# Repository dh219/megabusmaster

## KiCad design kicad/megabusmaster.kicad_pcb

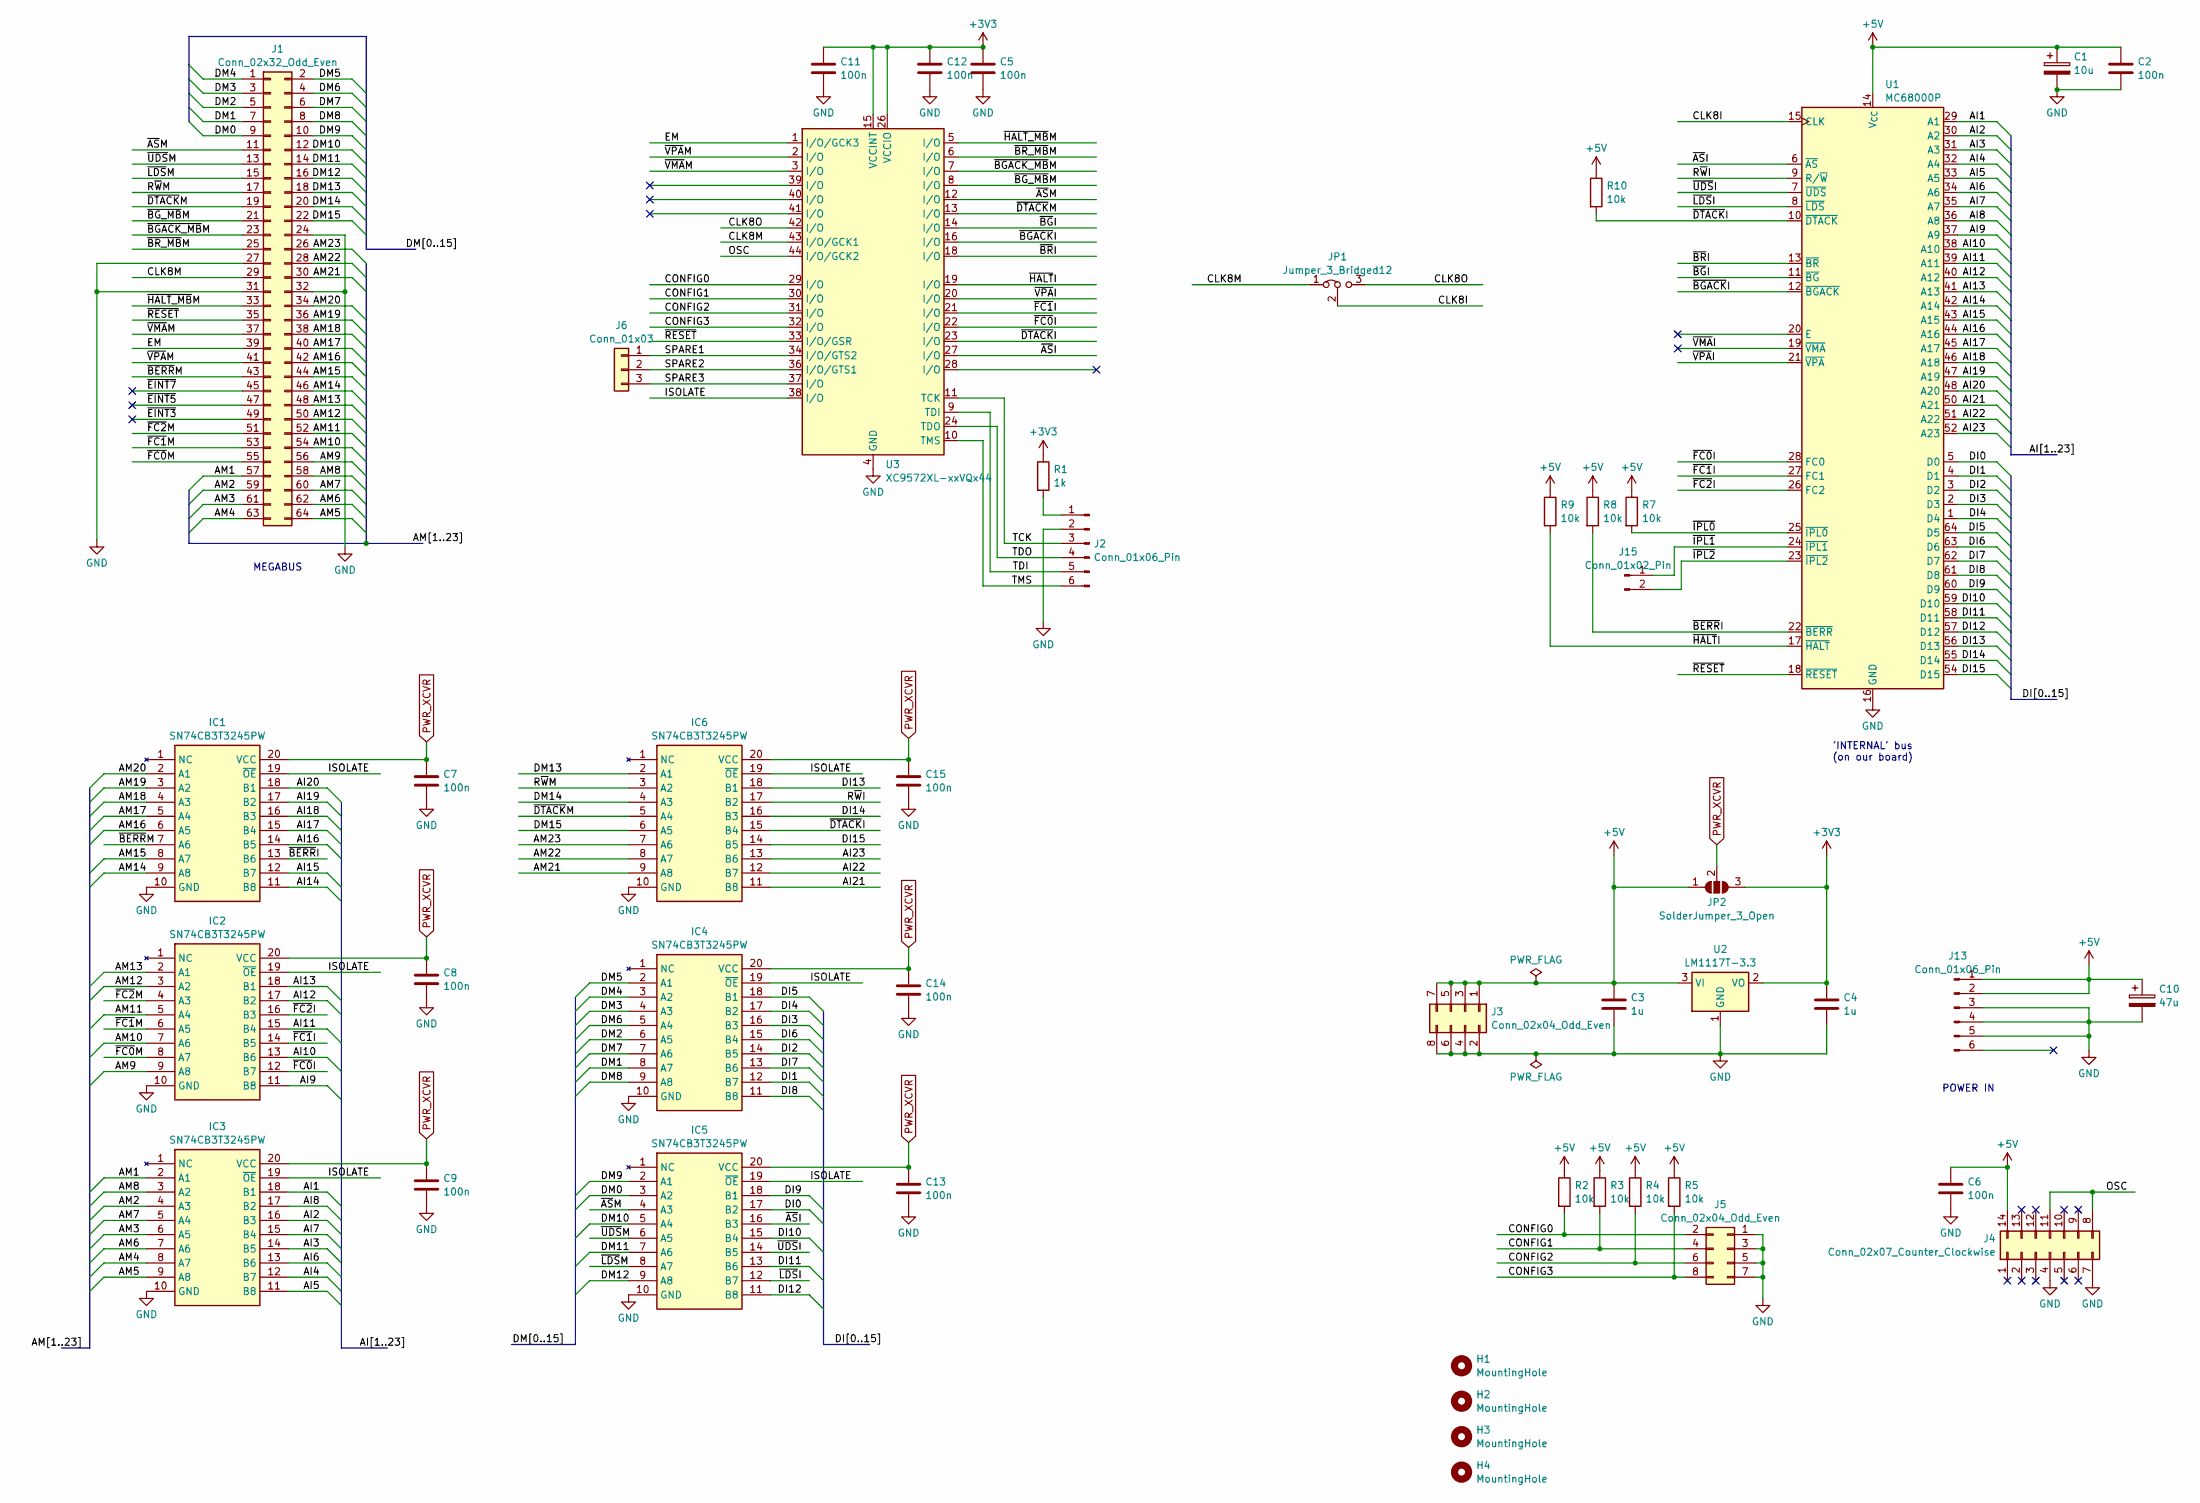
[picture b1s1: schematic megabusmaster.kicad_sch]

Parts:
C1: 10u; CP_Radial_D5.0mm_P2.50mm
C2, C5, C6, C7, C8, C9, C11, C12, C13, C14, C15: 100n; C_0805_2012Metric_Pad1.18x1.45mm_HandSolder
C3, C4: 1u; C_0805_2012Metric_Pad1.18x1.45mm_HandSolder
C10: 47u; CP_Radial_D5.0mm_P2.50mm
H1, H2, H3, H4: MountingHole; MountingHole_3.2mm_M3
IC1, IC2, IC3, IC4, IC5, IC6: SN74CB3T3245PW; TSSOP-20_4.4x6.5mm_P0.65mm; Manufacturer_Part_Number SN74CB3T3245PW; Mouser Part Number 595-SN74CB3T3245PW
J1: Conn_02x32_Odd_Even; PinSocket_2x32_P2.54mm_Vertical
J2, J13: Conn_01x06_Pin; PinHeader_1x06_P2.54mm_Vertical
J3, J5: Conn_02x04_Odd_Even; PinHeader_2x04_P2.54mm_Vertical
J4: Conn_02x07_Counter_Clockwise; DIP-14_W7.62mm_Socket
J6: Conn_01x03; SolderWire-0.25sqmm_1x03_P4.2mm_D0.65mm_OD1.7mm
J15: Conn_01x02_Pin; PinHeader_1x02_P2.54mm_Vertical
JP1: Jumper_3_Bridged12; PinHeader_1x03_P2.54mm_Vertical
JP2: SolderJumper_3_Open; SolderJumper-3_P1.3mm_Open_RoundedPad1.0x1.5mm
R1: 1k; R_0805_2012Metric_Pad1.20x1.40mm_HandSolder
R2, R3, R4, R5, R7, R8, R9, R10: 10k; R_0805_2012Metric_Pad1.20x1.40mm_HandSolder
U1: MC68000P; DIP-64_W22.86mm
U2: LM1117T-3.3; SOT-223-3_TabPin2
U3: XC9572XL-xxVQx44; TQFP-44_10x10mm_P0.8mm

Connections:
+3V3: C4.1, C5.1, C11.1, C12.1, JP2.3 (B), R1.1, U2.2 (VO), U3.15 (VCCINT), U3.26 (VCCIO), U3.35 (VCCINT)
+5V: C1.1, C2.1, C3.1, C6.1, C10.1, J3.1, J3.3, J3.5, J3.7, J4.14, J13.1, J13.2, JP2.1 (A), R2.1, R3.1, R4.1, R5.1, R7.1, R8.1, R9.1, R10.1, U1.14 (V_{CC}), U1.49 (V_{CC}), U2.3 (VI)
/AI1: IC3.18 (B1), U1.29 (A1)
/AI2: IC3.16 (B3), U1.30 (A2)
/AI3: IC3.14 (B5), U1.31 (A3)
/AI4: IC3.12 (B7), U1.32 (A4)
/AI5: IC3.11 (B8), U1.33 (A5)
/AI6: IC3.13 (B6), U1.34 (A6)
/AI7: IC3.15 (B4), U1.35 (A7)
/AI8: IC3.17 (B2), U1.36 (A8)
/AI9: IC2.11 (B8), U1.37 (A9)
/AI10: IC2.13 (B6), U1.38 (A10)
/AI11: IC2.15 (B4), U1.39 (A11)
/AI12: IC2.17 (B2), U1.40 (A12)
/AI13: IC2.18 (B1), U1.41 (A13)
/AI14: IC1.11 (B8), U1.42 (A14)
/AI15: IC1.12 (B7), U1.43 (A15)
/AI16: IC1.14 (B5), U1.44 (A16)
/AI17: IC1.15 (B4), U1.45 (A17)
/AI18: IC1.16 (B3), U1.46 (A18)
/AI19: IC1.17 (B2), U1.47 (A19)
/AI20: IC1.18 (B1), U1.48 (A20)
/AI21: IC6.11 (B8), U1.50 (A21)
/AI22: IC6.12 (B7), U1.51 (A22)
/AI23: IC6.13 (B6), U1.52 (A23)
/AM1: IC3.2 (A1), J1.57
/AM2: IC3.4 (A3), J1.59
/AM3: IC3.6 (A5), J1.61
/AM4: IC3.8 (A7), J1.63
/AM5: IC3.9 (A8), J1.64
/AM6: IC3.7 (A6), J1.62
/AM7: IC3.5 (A4), J1.60
/AM8: IC3.3 (A2), J1.58
/AM9: IC2.9 (A8), J1.56
/AM10: IC2.7 (A6), J1.54
/AM11: IC2.5 (A4), J1.52
/AM12: IC2.3 (A2), J1.50
/AM13: IC2.2 (A1), J1.48
/AM14: IC1.9 (A8), J1.46
/AM15: IC1.8 (A7), J1.44
/AM16: IC1.6 (A5), J1.42
/AM17: IC1.5 (A4), J1.40
/AM18: IC1.4 (A3), J1.38
/AM19: IC1.3 (A2), J1.36
/AM20: IC1.2 (A1), J1.34
/AM21: IC6.9 (A8), J1.30
/AM22: IC6.8 (A7), J1.28
/AM23: IC6.7 (A6), J1.26
/CLK8I: JP1.2 (C), U1.15 (CLK)
/CLK8M: J1.29, JP1.1 (A), U3.43 (I/O/GCK1)
/CLK8O: JP1.3 (B), U3.42 (I/O)
/CONFIG0: J5.2, R2.2, U3.29 (I/O)
/CONFIG1: J5.4, R3.2, U3.30 (I/O)
/CONFIG2: J5.6, R4.2, U3.31 (I/O)
/CONFIG3: J5.8, R5.2, U3.32 (I/O)
/DI0: IC5.17 (B2), U1.5 (D0)
/DI1: IC4.12 (B7), U1.4 (D1)
/DI2: IC4.14 (B5), U1.3 (D2)
/DI3: IC4.16 (B3), U1.2 (D3)
/DI4: IC4.17 (B2), U1.1 (D4)
/DI5: IC4.18 (B1), U1.64 (D5)
/DI6: IC4.15 (B4), U1.63 (D6)
/DI7: IC4.13 (B6), U1.62 (D7)
/DI8: IC4.11 (B8), U1.61 (D8)
/DI9: IC5.18 (B1), U1.60 (D9)
/DI10: IC5.15 (B4), U1.59 (D10)
/DI11: IC5.13 (B6), U1.58 (D11)
/DI12: IC5.11 (B8), U1.57 (D12)
/DI13: IC6.18 (B1), U1.56 (D13)
/DI14: IC6.16 (B3), U1.55 (D14)
/DI15: IC6.14 (B5), U1.54 (D15)
/DM0: IC5.3 (A2), J1.9
/DM1: IC4.8 (A7), J1.7
/DM2: IC4.6 (A5), J1.5
/DM3: IC4.4 (A3), J1.3
/DM4: IC4.3 (A2), J1.1
/DM5: IC4.2 (A1), J1.2
/DM6: IC4.5 (A4), J1.4
/DM7: IC4.7 (A6), J1.6
/DM8: IC4.9 (A8), J1.8
/DM9: IC5.2 (A1), J1.10
/DM10: IC5.5 (A4), J1.12
/DM11: IC5.7 (A6), J1.14
/DM12: IC5.9 (A8), J1.16
/DM13: IC6.2 (A1), J1.18
/DM14: IC6.4 (A3), J1.20
/DM15: IC6.6 (A5), J1.22
/EM: J1.39, U3.1 (I/O/GCK3)
/ISOLATE: IC1.19 (~OE), IC2.19 (~OE), IC3.19 (~OE), IC4.19 (~OE), IC5.19 (~OE), IC6.19 (~OE), U3.38 (I/O)
/OSC: J4.8, J4.11, U3.44 (I/O/GCK2)
/R~WI: IC6.17 (B2), U1.9 (R/~W)
/R~WM: IC6.3 (A2), J1.17
/SPARE1: J6.1, U3.34 (I/O/GTS2)
/SPARE2: J6.2, U3.36 (I/O/GTS1)
/SPARE3: J6.3, U3.37 (I/O)
/TCK: J2.3, U3.11 (TCK)
/TDI: J2.5, U3.9 (TDI)
/TDO: J2.4, U3.24 (TDO)
/TMS: J2.6, U3.10 (TMS)
/~ASI: IC5.16 (B3), U1.6 (~AS), U3.27 (I/O)
/~ASM: IC5.4 (A3), J1.11, U3.12 (I/O)
/~BERRI: IC1.13 (B6), R8.2, U1.22 (~BERR)
/~BERRM: IC1.7 (A6), J1.43
/~BGACK_MBM: J1.23, U3.7 (I/O)
/~BGACKI: U1.12 (~BGACK), U3.16 (I/O)
/~BG_MBM: J1.21, U3.8 (I/O)
/~BGI: U1.11 (~BG), U3.14 (I/O)
/~BR_MBM: J1.25, U3.6 (I/O)
/~BRI: U1.13 (~BR), U3.18 (I/O)
/~DTACKI: IC6.15 (B4), R10.2, U1.10 (~DTACK), U3.23 (I/O)
/~DTACKM: IC6.5 (A4), J1.19, U3.13 (I/O)
/~EINT3: J1.49
/~EINT5: J1.47
/~EINT7: J1.45
/~FC0I: IC2.12 (B7), U1.28 (FC0), U3.22 (I/O)
/~FC0M: IC2.8 (A7), J1.55
/~FC1I: IC2.14 (B5), U1.27 (FC1), U3.21 (I/O)
/~FC1M: IC2.6 (A5), J1.53
/~FC2I: IC2.16 (B3), U1.26 (FC2)
/~FC2M: IC2.4 (A3), J1.51
/~HALT_MBM: J1.33, U3.5 (I/O)
/~HALTI: R9.2, U1.17 (~HALT), U3.19 (I/O)
/~IPL0: R7.2, U1.25 (~IPL0)
/~IPL1: J15.1, U1.24 (~IPL1)
/~IPL2: J15.2, U1.23 (~IPL2)
/~LDSI: IC5.12 (B7), U1.8 (~LDS)
/~LDSM: IC5.8 (A7), J1.15
/~RESET: J1.35, U1.18 (~RESET), U3.33 (I/O/GSR)
/~UDSI: IC5.14 (B5), U1.7 (~UDS)
/~UDSM: IC5.6 (A5), J1.13
/~VMAI: U1.19 (~VMA)
/~VMAM: J1.37, U3.3 (I/O)
/~VPAI: U1.21 (~VPA), U3.20 (I/O)
/~VPAM: J1.41, U3.2 (I/O)
GND: C1.2, C2.2, C3.2, C4.2, C5.2, C6.2, C7.2, C8.2, C9.2, C10.2, C11.2, C12.2, C13.2, C14.2, C15.2, IC1.10 (GND), IC2.10 (GND), IC3.10 (GND), IC4.10 (GND), IC5.10 (GND), IC6.10 (GND), J1.24, J1.27, J1.31, J1.32, J2.2, J3.2, J3.4, J3.6, J3.8, J4.4, J4.7, J5.1, J5.3, J5.5, J5.7, J13.3, J13.4, J13.5, U1.16 (GND), U1.53 (GND), U2.1 (GND), U3.4 (GND), U3.17 (GND), U3.25 (GND)
unnamed: J2.1, R1.2
PWR_XCVR: C7.1, C8.1, C9.1, C13.1, C14.1, C15.1, IC1.20 (VCC), IC2.20 (VCC), IC3.20 (VCC), IC4.20 (VCC), IC5.20 (VCC), IC6.20 (VCC), JP2.2 (C)

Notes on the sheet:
POWER IN
'INTERNAL' bus (on our board)
MEGABUS

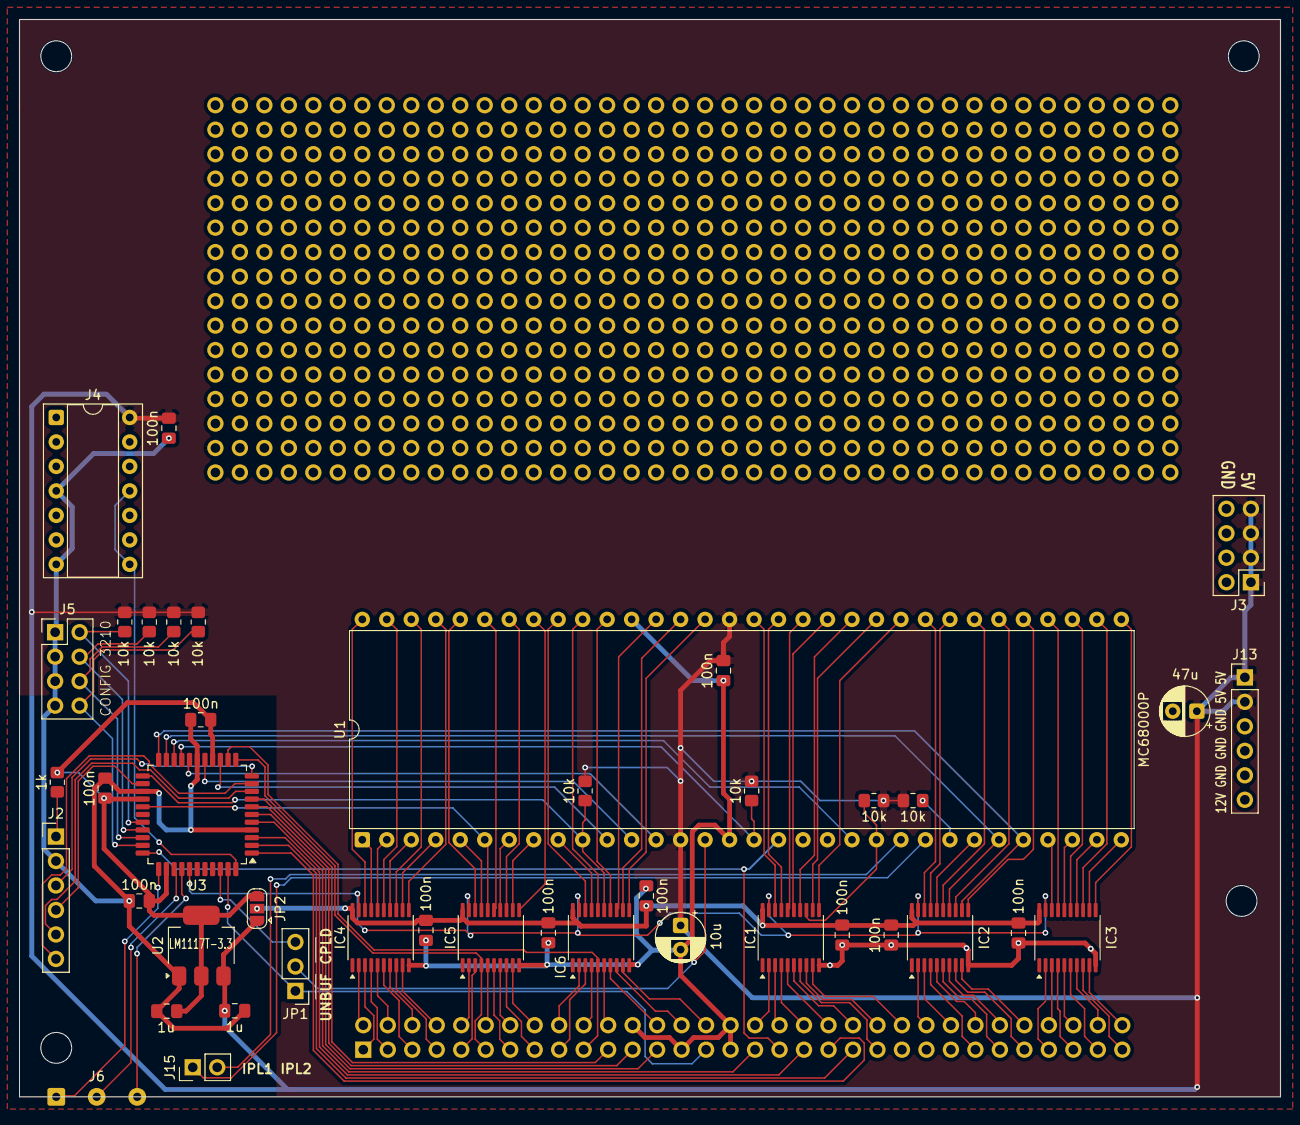
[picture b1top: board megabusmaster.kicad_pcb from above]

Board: 2 copper layers, 130.8 x 111.8 mm, 47 parts (1 on the bottom side), 133 nets.

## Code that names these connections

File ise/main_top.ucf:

#Created by Constraints Editor (xc9572xl-vq44-10) - 2026/09/22
NET "CLK8" TNM_NET = CLK8;
TIMESPEC TS_CLK8 = PERIOD "CLK8" 125 ns HIGH 50%;


NET "CLK8"  LOC = "P43" | BUFG=CLK ; 
NET "CLK8_O"  LOC = "P42" ; 

NET "RESET_MB" LOC = "P33" ;
NET "HALT_MB" LOC = "P5" ;
NET "BR_MB" LOC = "P6" ;
NET "BGACK_MB" LOC = "P7" ;
NET "BG_MB" LOC = "P8" ;
NET "DTACKM" LOC = "P13" ;
NET "VPA_MB" LOC = "P2" ;
NET "VMA_MB" LOC = "P3" ;
NET "ASM" LOC = "P12" ;

NET "BG_I" LOC = "P14" ;
NET "BGACK_I" LOC = "P16" ;
NET "BR_I" LOC = "P18" ;
NET "HALT_I" LOC = "P19" ;
NET "VPA_EXT" LOC = "P20" ;
NET "DTACK" LOC = "P23" ;
NET "AS_I" LOC = "P27" ;

NET "FC0" LOC = "P22" ;
NET "FC1" LOC = "P21" ;
NET "E" LOC = "P1" ;

NET "OSC" LOC = "P44" | BUFG=CLK ;
NET "CONFIGS<0>" LOC = "P29" ;
NET "CONFIGS<1>" LOC = "P30" ;
NET "CONFIGS<2>" LOC = "P31" ;
NET "CONFIGS<3>" LOC = "P32" ;
NET "SPARE<0>" LOC = "P34" ;
NET "SPARE<1>" LOC = "P36" ;
NET "SPARE<2>" LOC = "P37" ;
NET "ISOLATE" LOC = "P38" ;
